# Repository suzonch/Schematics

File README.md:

# schematics

- Project File - LED_test.pro
- Schematics - LED_test.sch
- PCB File - LED_test.kicad_pcb

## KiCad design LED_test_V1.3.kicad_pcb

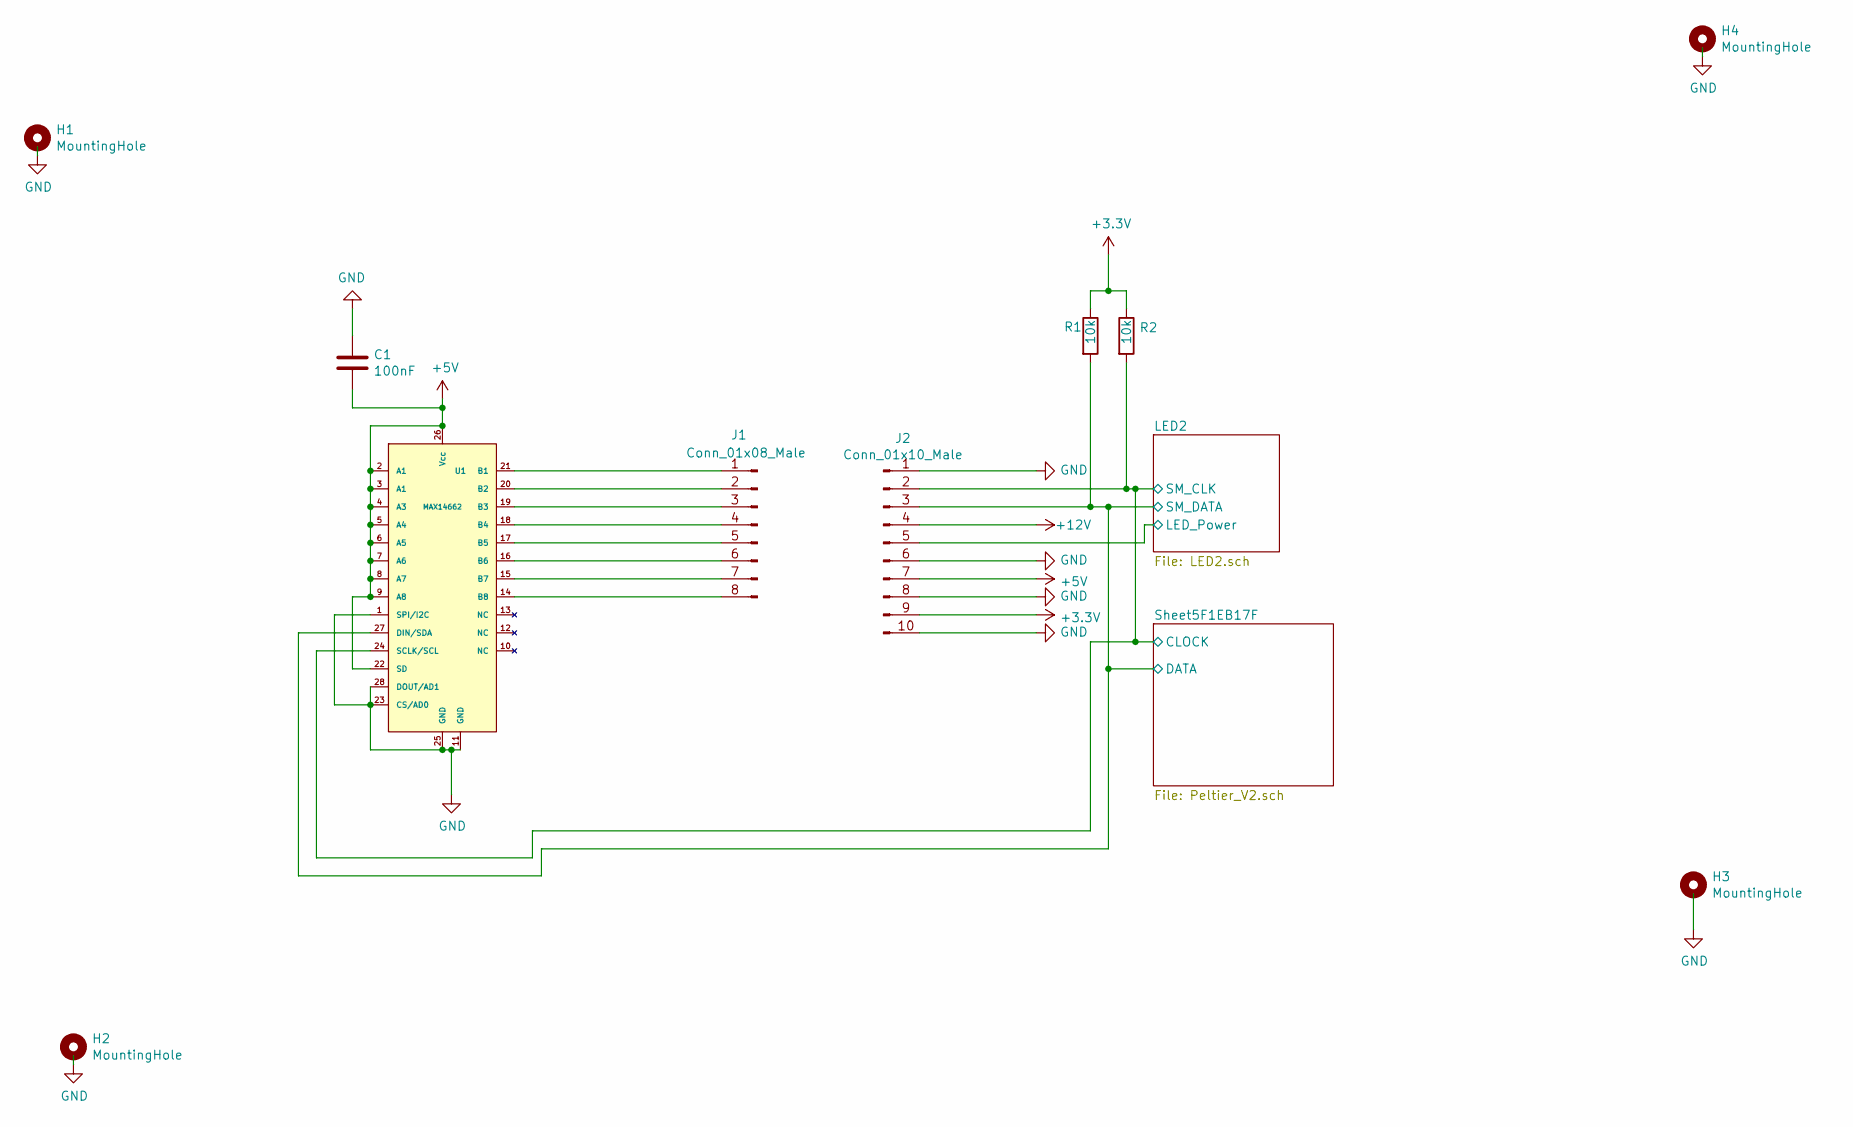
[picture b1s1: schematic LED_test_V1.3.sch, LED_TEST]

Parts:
C1: 100nF; C_0603_1608Metric_Pad1.05x0.95mm_HandSolder
H1, H2, H3, H4: MountingHole; MountingHole_3.5mm_Pad
J1: Conn_01x08_Male; PinHeader_1x08_P2.54mm_Vertical
J2: Conn_01x10_Male; PinHeader_1x10_P2.54mm_Vertical
R1, R2: 10k; R_0603_1608Metric_Pad1.05x0.95mm_HandSolder
U1: MAX14662; QFN-28-1EP_4x4mm_P0.4mm_EP2.6x2.6mm_ThermalVias

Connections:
+3V3: J2.9, R1.1, R2.1; also elsewhere on the board
+5V: C1.2, J2.7, U1.2 (A1), U1.3 (A1), U1.4 (A3), U1.5 (A4), U1.6 (A5), U1.7 (A6), U1.8 (A7), U1.9 (A8), U1.22 (SD), U1.26 (Vcc); also elsewhere on the board
+12V: J2.4; also elsewhere on the board
/LED2/LED_Power: J2.5; also elsewhere on the board
/Sheet5F1EB17F/CLOCK: J2.2, R2.2, U1.24 (SCLK/SCL); also elsewhere on the board
/Sheet5F1EB17F/DATA: J2.3, R1.2, U1.27 (DIN/SDA); also elsewhere on the board
GND: C1.1, H1.1, H2.1, H3.1, H4.1, J2.1, J2.6, J2.8, J2.10, U1.1 (SPI/I2C), U1.11 (GND), U1.23 (CS/AD0), U1.25 (GND), U1.28 (DOUT/AD1), U1.29 (EP); also elsewhere on the board
unnamed: J1.1, U1.21 (B1)
unnamed: J1.2, U1.20 (B2)
unnamed: J1.3, U1.19 (B3)
unnamed: J1.4, U1.18 (B4)
unnamed: J1.5, U1.17 (B5)
unnamed: J1.6, U1.16 (B6)
unnamed: J1.7, U1.15 (B7)
unnamed: J1.8, U1.14 (B8)

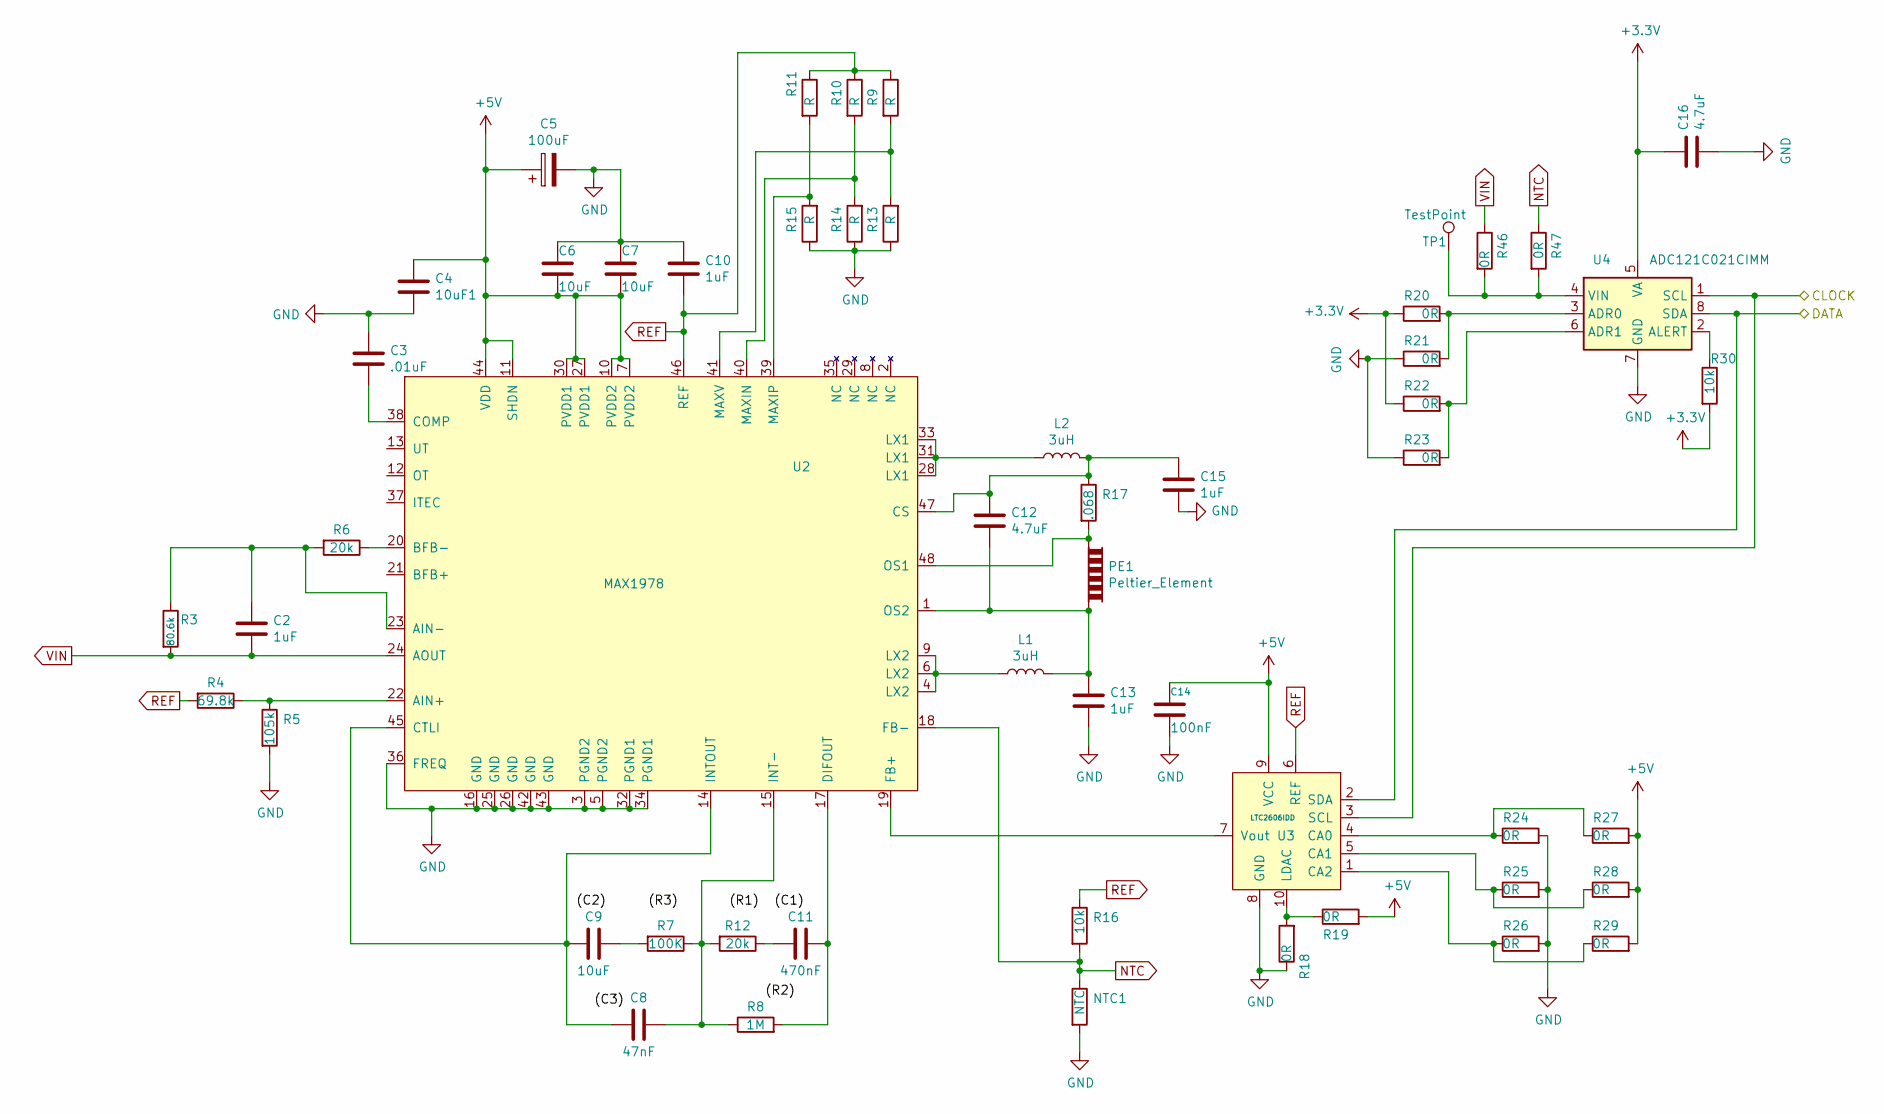
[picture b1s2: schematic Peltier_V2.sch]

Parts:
C2, C10, C13, C15: 1uF; C_0805_2012Metric_Pad1.15x1.40mm_HandSolder
C3: .01uF; C_0805_2012Metric_Pad1.15x1.40mm_HandSolder
C4: 10uF1; C_0805_2012Metric_Pad1.15x1.40mm_HandSolder
C5: 100uF; CP_EIA-7343-15_Kemet-W_Pad2.25x2.55mm_HandSolder
C6, C7, C9: 10uF; C_0805_2012Metric_Pad1.15x1.40mm_HandSolder
C8: 47nF; C_0805_2012Metric_Pad1.15x1.40mm_HandSolder
C11: 470nF; C_0805_2012Metric_Pad1.15x1.40mm_HandSolder
C12, C16: 4.7uF; C_0805_2012Metric_Pad1.15x1.40mm_HandSolder
C14: 100nF; C_0603_1608Metric_Pad1.05x0.95mm_HandSolder
L1, L2: 3uH; L_Coilcraft_XAL60xx_6.36x6.56mm
NTC1: NTC; SolderWire-0.1sqmm_1x02_P3.6mm_D0.4mm_OD1mm
PE1: Peltier_Element; SolderWire-1sqmm_1x02_P5.4mm_D1.4mm_OD2.7mm
R3: 80.6k; R_0603_1608Metric_Pad1.05x0.95mm_HandSolder
R4: 69.8k; R_0603_1608Metric_Pad1.05x0.95mm_HandSolder
R5: 105k; R_0603_1608Metric_Pad1.05x0.95mm_HandSolder
R6, R12: 20k; R_0603_1608Metric_Pad1.05x0.95mm_HandSolder
R7: 100K; R_0603_1608Metric_Pad1.05x0.95mm_HandSolder
R8: 1M; R_0603_1608Metric_Pad1.05x0.95mm_HandSolder
R9, R10, R11, R13, R14, R15: R; R_0603_1608Metric_Pad1.05x0.95mm_HandSolder
R16, R30: 10k; R_0603_1608Metric_Pad1.05x0.95mm_HandSolder
R17: .068; R_0603_1608Metric_Pad1.05x0.95mm_HandSolder
R18, R19, R20, R21, R22, R23, R24, R25, R26, R27, R28, R29, R46, R47: 0R; R_0402_1005Metric
TP1: TestPoint; TestPoint_Pad_D3.0mm
U2: MAX1978; QFN-48-1EP_7x7mm_P0.5mm_EP5.45x5.45mm_ThermalVias
U3: LTC2606IDD; DFN-10-1EP_3x3mm_P0.5mm_EP1.65x2.38mm_ThermalVias
U4: ADC121C021CIMM; MSOP-8_3x3mm_P0.65mm

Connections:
+3V3: C16.1, R20.1, R22.1, R30.2, U4.5 (VA); also elsewhere on the board
+5V: C4.1, C5.1, C6.2, C7.2, C14.1, R19.2, R27.2, R28.2, R29.2, U2.7 (PVDD2), U2.10 (PVDD2), U2.11 (SHDN), U2.27 (PVDD1), U2.30 (PVDD1), U2.44 (VDD), U3.9 (VCC); also elsewhere on the board
/Sheet5F1EB17F/CLOCK: U3.3 (SCL), U4.1 (SCL); also elsewhere on the board
/Sheet5F1EB17F/DATA: U3.2 (SDA), U4.8 (SDA); also elsewhere on the board
GND: C3.1, C4.2, C5.2, C6.1, C7.1, C10.1, C13.2, C14.2, C15.2, C16.2, NTC1.2, R5.2, R13.1, R14.1, R15.1, R18.1, R21.1, R23.1, R24.2, R25.2, R26.2, U2.3 (PGND2), U2.5 (PGND2), U2.16 (GND), U2.25 (GND), U2.26 (GND), U2.32 (PGND1), U2.34 (PGND1), U2.36 (FREQ), U2.42 (GND), U2.43 (GND), U2.49 (EP), U3.8 (GND), U3.11 (EP), U4.7 (GND); also elsewhere on the board
NTC: NTC1.1, R16.2, R47.1, U2.18 (FB-)
unnamed: C2.1, R3.1, R6.2, U2.23 (AIN-)
unnamed: C3.2, U2.38 (COMP)
unnamed: C8.1, C9.2, U2.14 (INTOUT), U2.45 (CTLI)
unnamed: C8.2, R7.1, R8.1, R12.2, U2.15 (INT-)
unnamed: C9.1, R7.2
unnamed: C11.1, R8.2, U2.17 (DIFOUT)
unnamed: C11.2, R12.1
unnamed: C12.1, C15.1, L2.2, R17.1, U2.47 (CS)
unnamed: C12.2, C13.1, L1.2, PE1.2, U2.1 (OS2)
unnamed: L1.1, U2.4 (LX2), U2.6 (LX2), U2.9 (LX2)
unnamed: L2.1, U2.28 (LX1), U2.31 (LX1), U2.33 (LX1)
unnamed: PE1.1, R17.2, U2.48 (OS1)
unnamed: R4.1, R5.1, U2.22 (AIN+)
unnamed: R6.1, U2.20 (BFB-)
unnamed: R10.2, R14.2, U2.40 (MAXIN)
unnamed: R11.2, R15.2, U2.39 (MAXIP)
unnamed: R9.2, R13.2, U2.41 (MAXV)
unnamed: R18.2, R19.1, U3.10 (LDAC)
unnamed: R20.2, R21.2, U4.3 (ADR0)
unnamed: R22.2, R23.2, U4.6 (ADR1)
unnamed: R24.1, R27.1, U3.4 (CA0)
unnamed: R25.1, R28.1, U3.5 (CA1)
unnamed: R26.1, R29.1, U3.1 (CA2)
unnamed: R30.1, U4.2 (ALERT)
unnamed: R46.2, R47.2, TP1.1, U4.4 (VIN)
unnamed: U2.19 (FB+), U3.7 (Vout)
REF: C10.2, R4.2, R9.1, R10.1, R11.1, R16.1, U2.46 (REF), U3.6 (REF)
VIN: C2.2, R3.2, R46.1, U2.24 (AOUT)

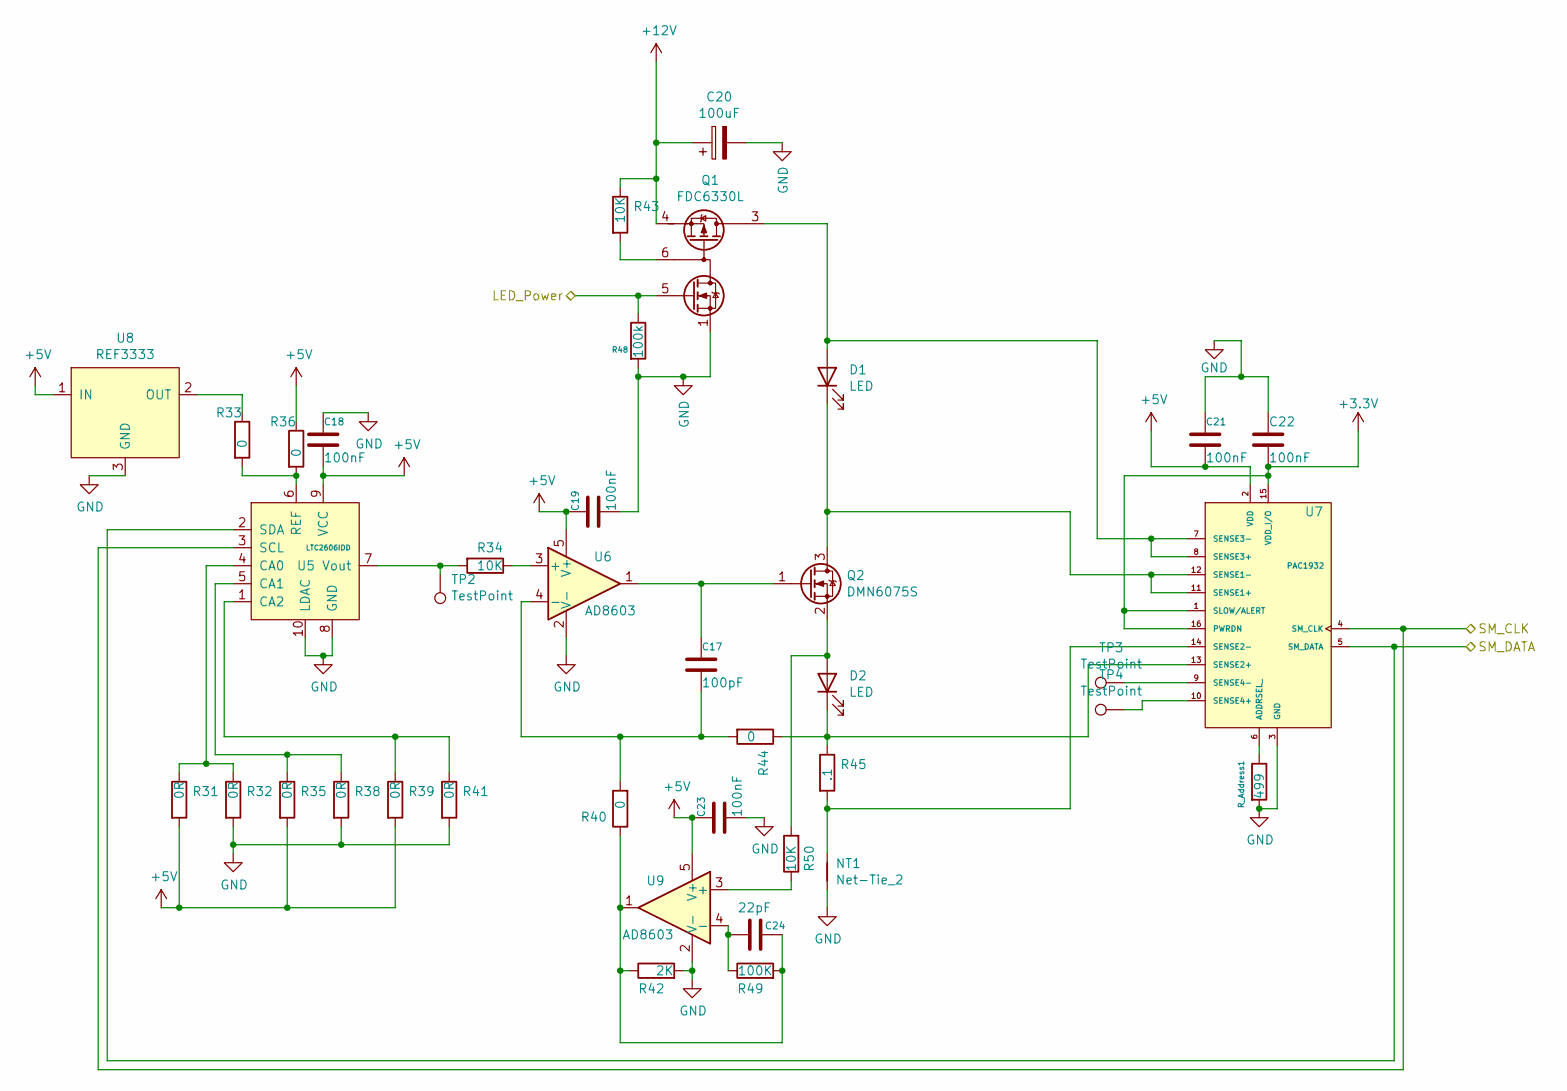
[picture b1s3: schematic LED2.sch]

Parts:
C17: 100pF; C_0603_1608Metric_Pad1.05x0.95mm_HandSolder
C18, C19, C21, C22, C23: 100nF; C_0603_1608Metric_Pad1.05x0.95mm_HandSolder
C20: 100uF; CP_EIA-7343-15_Kemet-W_Pad2.25x2.55mm_HandSolder
C24: 22pF; C_0603_1608Metric_Pad1.05x0.95mm_HandSolder
D1, D2: LED; LED_D3.0mm
NT1: Net-Tie_2; NetTie-2_SMD_Pad0.5mm
Q1: FDC6330L; TSOT-23-6
Q2: DMN6075S; SOT-23
R31, R32, R35, R38, R39, R41: 0R; R_0402_1005Metric
R33, R36, R40, R44: 0; R_0402_1005Metric
R34, R43, R50: 10K; R_0603_1608Metric_Pad1.05x0.95mm_HandSolder
R42: 2K; R_0603_1608Metric_Pad1.05x0.95mm_HandSolder
R45: .1; R_1206_3216Metric_Pad1.42x1.75mm_HandSolder
R48: 100k; R_0603_1608Metric_Pad1.05x0.95mm_HandSolder
R49: 100K; R_0603_1608Metric_Pad1.05x0.95mm_HandSolder
R_Address1: 499; R_0603_1608Metric_Pad1.05x0.95mm_HandSolder
TP2, TP3, TP4: TestPoint; TestPoint_Pad_D1.0mm
U5: LTC2606IDD; DFN-10-1EP_3x3mm_P0.5mm_EP1.65x2.38mm_ThermalVias
U6, U9: AD8603; TSOT-23-5
U7: PAC1932; QFN-16-1EP_4x4mm_P0.65mm_EP2.5x2.5mm_ThermalVias
U8: REF3333; SOT-23

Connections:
+3V3: C22.2, U7.1 (SLOW/ALERT), U7.15 (VDD_I/O), U7.16 (PWRDN); also elsewhere on the board
+5V: C18.2, C19.1, C21.2, C23.1, R31.2, R35.2, R36.1, R39.2, U5.9 (VCC), U6.5 (V+), U7.2 (VDD), U8.1 (IN), U9.5 (V+); also elsewhere on the board
+12V: C20.1, Q1.4 (S2), R43.1; also elsewhere on the board
/LED2/LED_Power: Q1.5 (G1), R48.1; also elsewhere on the board
/Sheet5F1EB17F/CLOCK: U5.3 (SCL), U7.4 (SM_CLK); also elsewhere on the board
/Sheet5F1EB17F/DATA: U5.2 (SDA), U7.5 (SM_DATA); also elsewhere on the board
GND: C18.1, C19.2, C20.2, C21.1, C22.1, C23.2, NT1.2, Q1.1 (S1), R32.2, R38.2, R41.2, R42.2, R48.2, R_Address1.2, U5.8 (GND), U5.10 (LDAC), U5.11 (EP), U6.2 (V-), U7.3 (GND), U8.3 (GND), U9.2 (V-); also elsewhere on the board
unnamed: C17.1, Q2.1 (G), U6.1
unnamed: C17.2, R40.2, R44.2, U6.4 (-)
unnamed: C24.1, R40.1, R42.1, R49.2, U9.1
unnamed: C24.2, R49.1, U9.4 (-)
unnamed: D1.1 (K), Q2.3 (D), U7.11 (SENSE1+), U7.12 (SENSE1-)
unnamed: D1.2 (A), Q1.2 (D2), Q1.3 (D2), U7.7 (SENSE3-), U7.8 (SENSE3+)
unnamed: D2.1 (K), R44.1, R45.1, U7.13 (SENSE2+)
unnamed: D2.2 (A), Q2.2 (S), R50.2
unnamed: NT1.1, R45.2, U7.14 (SENSE2-)
unnamed: Q1.6 (D1), R43.2
unnamed: R31.1, R32.1, U5.4 (CA0)
unnamed: R33.1, U8.2 (OUT)
unnamed: R33.2, R36.2, U5.6 (REF)
unnamed: R34.1, U6.3 (+)
unnamed: R34.2, TP2.1, U5.7 (Vout)
unnamed: R35.1, R38.1, U5.5 (CA1)
unnamed: R39.1, R41.1, U5.1 (CA2)
unnamed: R50.1, U9.3 (+)
unnamed: R_Address1.1, U7.6 (ADDRSEL_)
unnamed: TP3.1, U7.9 (SENSE4-)
unnamed: TP4.1, U7.10 (SENSE4+)

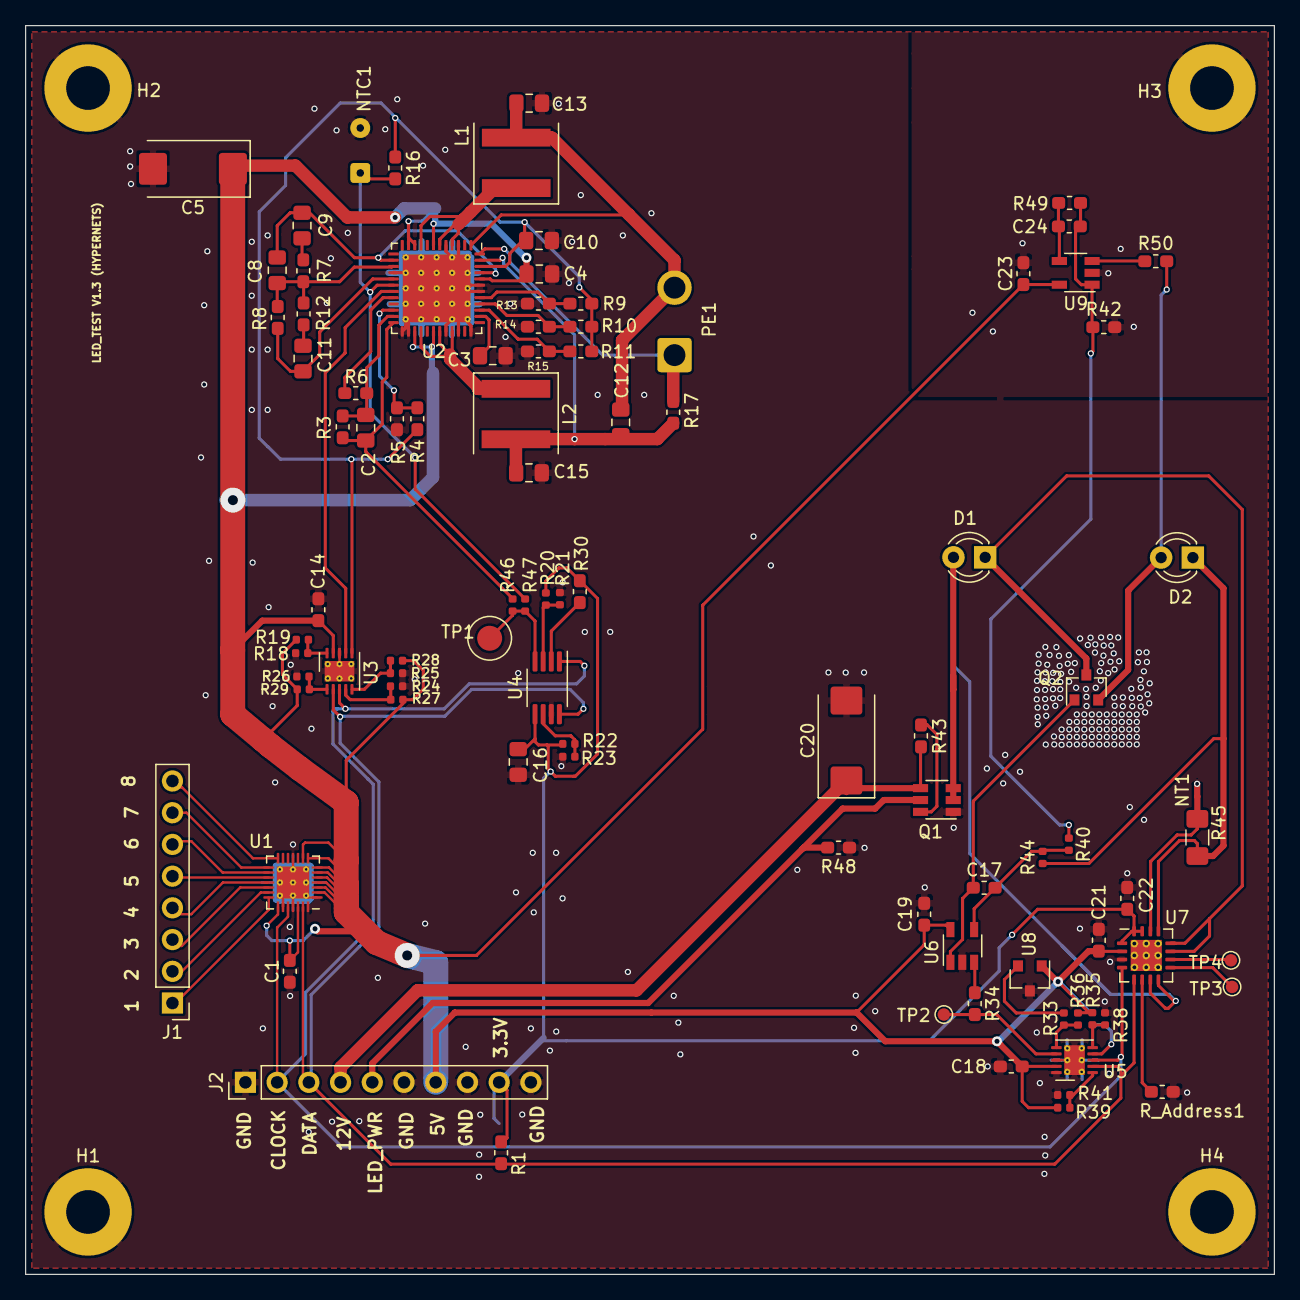
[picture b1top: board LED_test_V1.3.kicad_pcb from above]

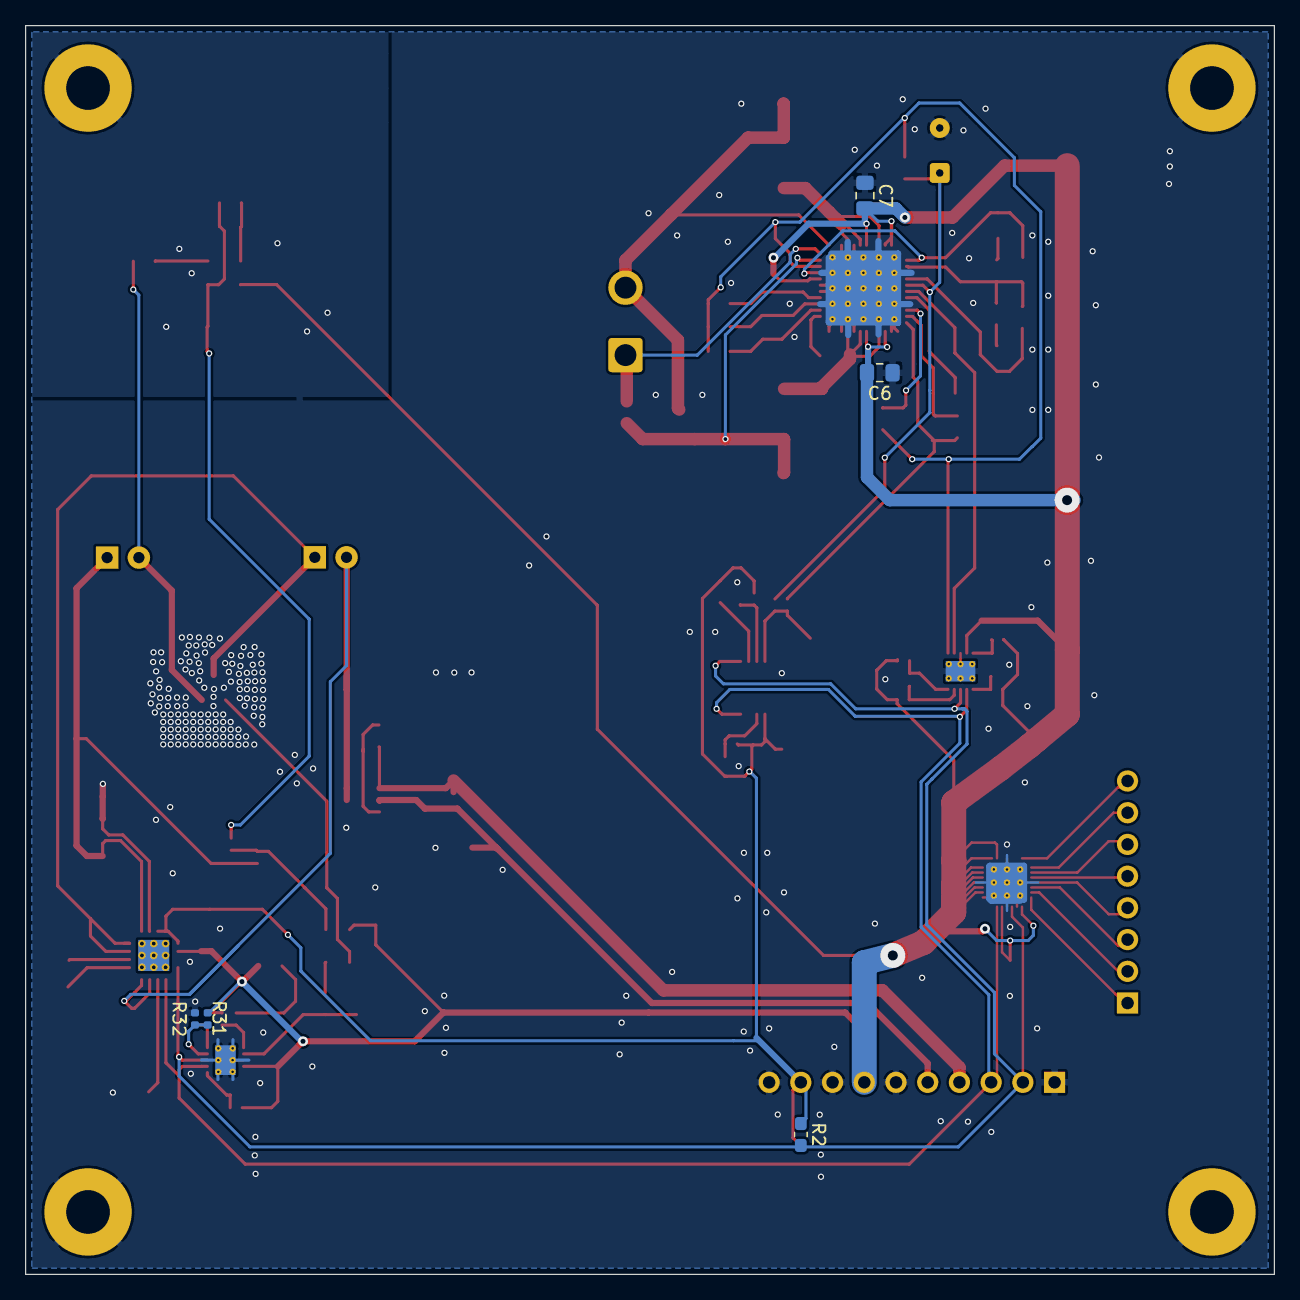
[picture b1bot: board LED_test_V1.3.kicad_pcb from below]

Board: 2 copper layers, 100.0 x 100.0 mm, 102 parts (5 on the bottom side), 65 nets.

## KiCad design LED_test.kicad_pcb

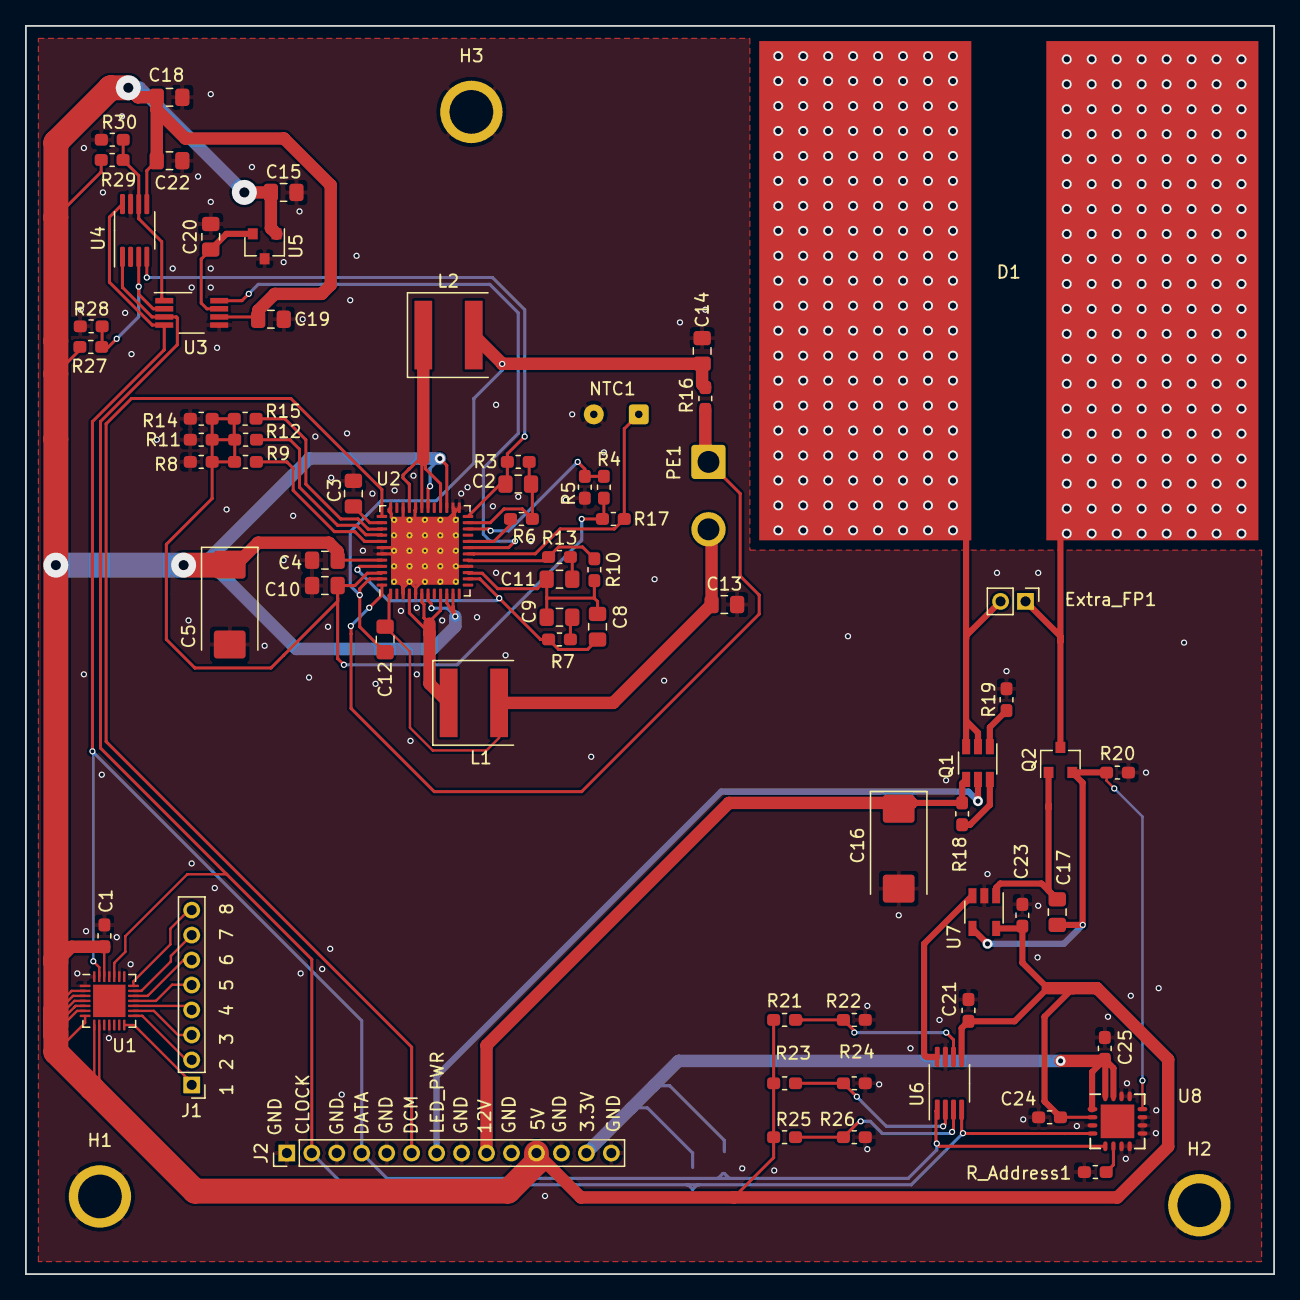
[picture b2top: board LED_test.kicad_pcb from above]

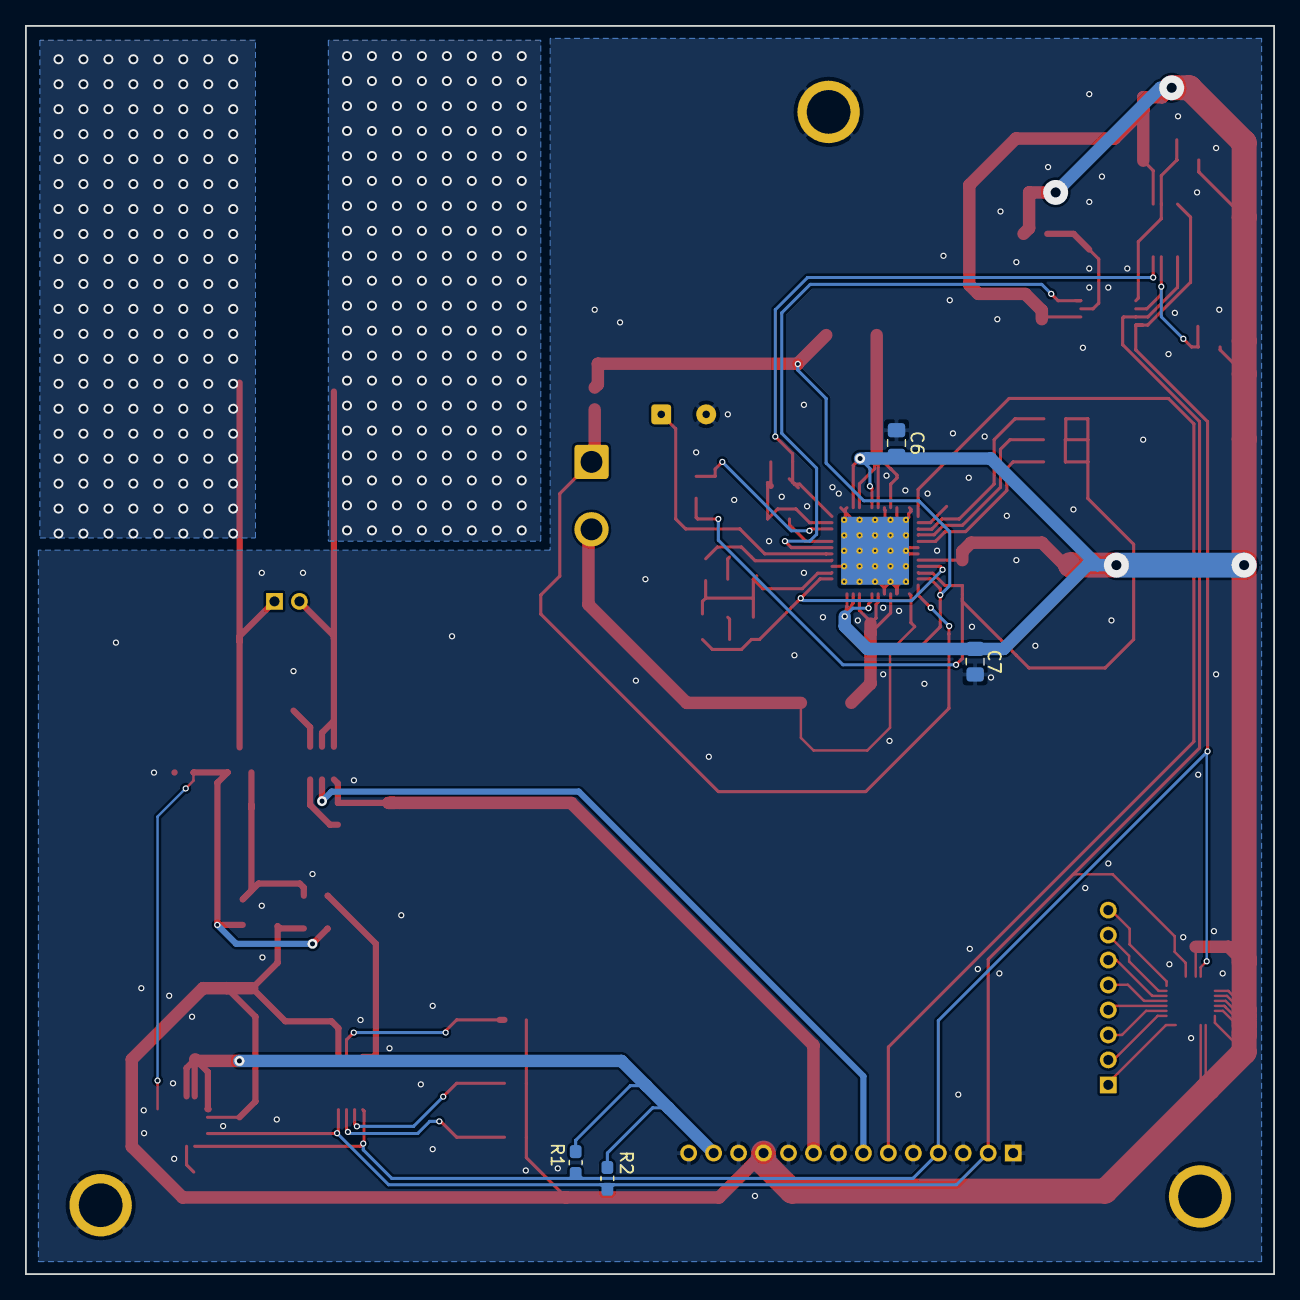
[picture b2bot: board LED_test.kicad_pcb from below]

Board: 2 copper layers, 100.0 x 100.0 mm, 77 parts (4 on the bottom side), 51 nets.

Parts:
C1, C21, C23, C24, C25: 100nF; C_0603_1608Metric_Pad1.05x0.95mm_HandSolder
C2, C10, C13, C14, C15, C19, C20, C22: 1uF; C_0805_2012Metric_Pad1.15x1.40mm_HandSolder
C3: .01uF; C_0805_2012Metric_Pad1.15x1.40mm_HandSolder
C4: 10uF1; C_0805_2012Metric_Pad1.15x1.40mm_HandSolder
C5, C16: 100uF; CP_EIA-7343-15_Kemet-W_Pad2.25x2.55mm_HandSolder
C6, C7, C9: 10uF; C_0805_2012Metric_Pad1.15x1.40mm_HandSolder
C8: .047uF; C_0805_2012Metric_Pad1.15x1.40mm_HandSolder
C11: .47uF; C_0805_2012Metric_Pad1.15x1.40mm_HandSolder
C12, C18: 4.7uF; C_0805_2012Metric_Pad1.15x1.40mm_HandSolder
C17: .1uF; C_0805_2012Metric_Pad1.15x1.40mm_HandSolder
D1: LED; LED_PAD
Extra_FP1: LED; PinHeader_1x02_P2.00mm_Vertical
H1, H2, H3: MountingHole; MountingHole_3.5mm_Pad
J1: Conn_01x08_Male; PinHeader_1x08_P2.00mm_Vertical
J2: Conn_01x14_Male; PinHeader_1x14_P2.00mm_Vertical
L1, L2: 3uH; L_Coilcraft_XAL60xx_6.36x6.56mm
NTC1: NTC; SolderWire-0.1sqmm_1x02_P3.6mm_D0.4mm_OD1mm
PE1: Peltier_Element; SolderWire-1sqmm_1x02_P5.4mm_D1.4mm_OD2.7mm
Q1: FDC6330L; TSOT-23-6
Q2: DMN6075S; SOT-23
R1, R2, R17: 10k; R_0603_1608Metric_Pad1.05x0.95mm_HandSolder
R3: 80.6k; R_0603_1608Metric_Pad1.05x0.95mm_HandSolder
R4: 69.8k; R_0603_1608Metric_Pad1.05x0.95mm_HandSolder
R5: 105k; R_0603_1608Metric_Pad1.05x0.95mm_HandSolder
R6, R13: 20k; R_0603_1608Metric_Pad1.05x0.95mm_HandSolder
R7: 100K; R_0603_1608Metric_Pad1.05x0.95mm_HandSolder
R8, R9, R11, R12, R14, R15: R; R_0603_1608Metric_Pad1.05x0.95mm_HandSolder
R10: 1M; R_0603_1608Metric_Pad1.05x0.95mm_HandSolder
R16: .068; R_0603_1608Metric_Pad1.05x0.95mm_HandSolder
R18: 100; R_0603_1608Metric_Pad1.05x0.95mm_HandSolder
R19: 1k; R_0603_1608Metric_Pad1.05x0.95mm_HandSolder
R20: .1; R_0603_1608Metric_Pad1.05x0.95mm_HandSolder
R21, R22, R23, R24, R25, R26, R27, R28, R29, R30: 0R; R_0603_1608Metric_Pad1.05x0.95mm_HandSolder
R_Address1: 499; R_0603_1608Metric_Pad1.05x0.95mm_HandSolder
U1: MAX14662; QFN-28-1EP_4x4mm_P0.4mm_EP2.6x2.6mm
U2: MAX1978; QFN-48-1EP_7x7mm_P0.5mm_EP5.45x5.45mm_ThermalVias
U3: DAC081C085; VSSOP-8_3.0x3.0mm_P0.65mm
U4: ADC101C021CIMM; MSOP-8_3x3mm_P0.65mm
U5: REF3333; SOT-23
U6: LTC1669IMS8; MSOP-8_3x3mm_P0.65mm
U7: AD8603; TSOT-23-5
U8: PAC1931; UQFN-16-1EP_4x4mm_P0.65mm_EP2.7x2.7mm

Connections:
+3V3: C25.2, J2.13, R1.1, R2.1, U8.1, U8.15, U8.16
+5V: C1.2, C4.1, C5.1, C6.2, C7.2, C15.1, C18.2, C19.1, C21.2, C22.1, C23.1, C24.2, J2.11, R21.2, R23.2, R25.2, R27.1, R29.1, U1.2, U1.3, U1.4, U1.5, U1.6, U1.7, U1.8, U1.9, U1.26, U2.7, U2.10, U2.11, U2.27, U2.30, U2.44, U3.6, U4.5, U5.1, U6.5, U7.5, U8.2
+12V: C16.1, J2.9, Q1.4, R18.1
/LED2/LED_Power: J2.7, Q1.5
/Sheet5F1EB17F/CLOCK: J2.2, R2.2, U1.24, U3.3, U4.1, U6.4, U8.4
/Sheet5F1EB17F/DATA: J2.4, R1.2, U1.27, U3.4, U4.8, U6.1, U8.5
/Sheet5F1EB17F/DC_Current_Monitor: J2.6, U2.37
GND: C1.1, C3.1, C4.2, C5.2, C6.1, C7.1, C10.1, C13.2, C14.2, C15.2, C16.2, C18.1, C19.2, C20.2, C21.1, C22.2, C23.2, C24.1, C25.1, H1.1, H2.1, H3.1, J2.1, J2.3, J2.5, J2.8, J2.10, J2.12, J2.14, NTC1.2, R5.2, R8.1, R11.1, R14.1, R19.2, R20.2, R22.2, R24.2, R26.2, R28.1, R30.1, R_Address1.2, U1.1, U1.11, U1.23, U1.25, U1.28, U2.3, U2.5, U2.16, U2.25, U2.26, U2.32, U2.34, U2.36, U2.42, U2.43, U2.49, U3.5, U4.7, U5.3, U6.7, U7.2, U8.3, U8.7, U8.8, U8.9, U8.10, U8.11, U8.13, U8.14
unnamed: C2.1, R3.1, R6.2, U2.23
unnamed: C3.2, U2.38
unnamed: C8.1, R7.2, U2.14, U2.45
unnamed: C9.2, R7.1
unnamed: C11.1, R13.2
unnamed: C8.2, C9.1, C11.2, R10.1, U2.15
unnamed: C12.1, C14.1, L2.2, R16.1, U2.47
unnamed: C12.2, C13.1, L1.2, PE1.2, U2.1
unnamed: C17.1, Q2.1, U7.1
unnamed: C17.2, Q2.2, R20.1, U7.4, U8.12
unnamed: C20.1, U3.7, U5.2
unnamed: D1.1, Extra_FP1.1, Q2.3
unnamed: D1.2, Extra_FP1.2, Q1.2, Q1.3
unnamed: J1.1, U1.14
unnamed: J1.2, U1.15
unnamed: J1.3, U1.16
unnamed: J1.4, U1.17
unnamed: J1.5, U1.18
unnamed: J1.6, U1.19
unnamed: J1.7, U1.20
unnamed: J1.8, U1.21
unnamed: L1.1, U2.4, U2.6, U2.9
unnamed: L2.1, U2.28, U2.31, U2.33
unnamed: NTC1.1, R17.2, U2.18
unnamed: PE1.1, R16.2, U2.48
unnamed: Q1.1, R19.1
unnamed: Q1.6, R18.2
unnamed: R4.1, R5.1, U2.22
unnamed: R6.1, U2.20
unnamed: R9.2, U2.41
unnamed: R10.2, R13.1, U2.17
unnamed: R12.2, U2.40
unnamed: R15.2, U2.39
unnamed: R21.1, R22.1, U6.6
unnamed: R23.1, R24.1, U6.2
unnamed: R25.1, R26.1, U6.3
unnamed: R27.2, R28.2, U3.2, U4.3
unnamed: R29.2, R30.2, U3.1, U4.6
unnamed: R_Address1.1, U8.6
unnamed: U2.19, U3.8
unnamed: U6.8, U7.3
REF: C10.2, R4.2, R8.2, R9.1, R11.2, R12.1, R14.2, R15.1, R17.1, U2.46
VIN: C2.2, R3.2, U2.24, U4.4

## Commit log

2020-08-06 Current PCB
2020-08-10 READ ME
2020-12-28 LED_V2
2021-01-07 LED_Test_V1.3
2021-01-17 LED_Test_Board_V1.3
